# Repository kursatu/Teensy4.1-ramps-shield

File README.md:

# Teensy4.1-ramps-shield

This is a RAMPS shield/adapter for teensy4.1.\
The Marlin firmware now has support for teensy4.1.\
But, I couldn't find a ready-to-use HW.\
So, I've designed one for myself.\
It only has female headers at this time and I'll try to keep it this way.\
It is work in progress and not really in my priority list. But it is something super easy to do. \
The teensy4.1 work is still progressing, there may be pin changes and such.\
So I may not move very fast on it.\
Here is the schema https://github.com/kursatu/Teensy4.1-ramps-shield/blob/main/schema.png \
Here is the board https://github.com/kursatu/Teensy4.1-ramps-shield/blob/main/board.png \

Here is the pin mapping

Teensy4.1 | Mega2560/RAMPS
-|-
TODO | TODO

To do:
- [ ] Verify if all pins are properly mapped, using a RAMPS board and breadboard teensy4.1
- [ ] Get it verified by the people in github teensy4.1 thread
- [ ] Get it produced
- [ ] Find and way for people to order them inexpensively. Osh park charges $42 for 3 of them.

Completed tasks:
- [X] Complete all the pin connections. Completed on Oct/13/2020
- [X] Order RAMPS board. Completed on Oct/14/2020
Ordered this RAMP 1.6 board.\
They are supposedly pin compatible with RAMP 1.4 of reprap.\
https://www.amazon.com/gp/product/B07RF576WC/ref=ppx_yo_dt_b_asin_title_o00_s00?ie=UTF8&psc=1

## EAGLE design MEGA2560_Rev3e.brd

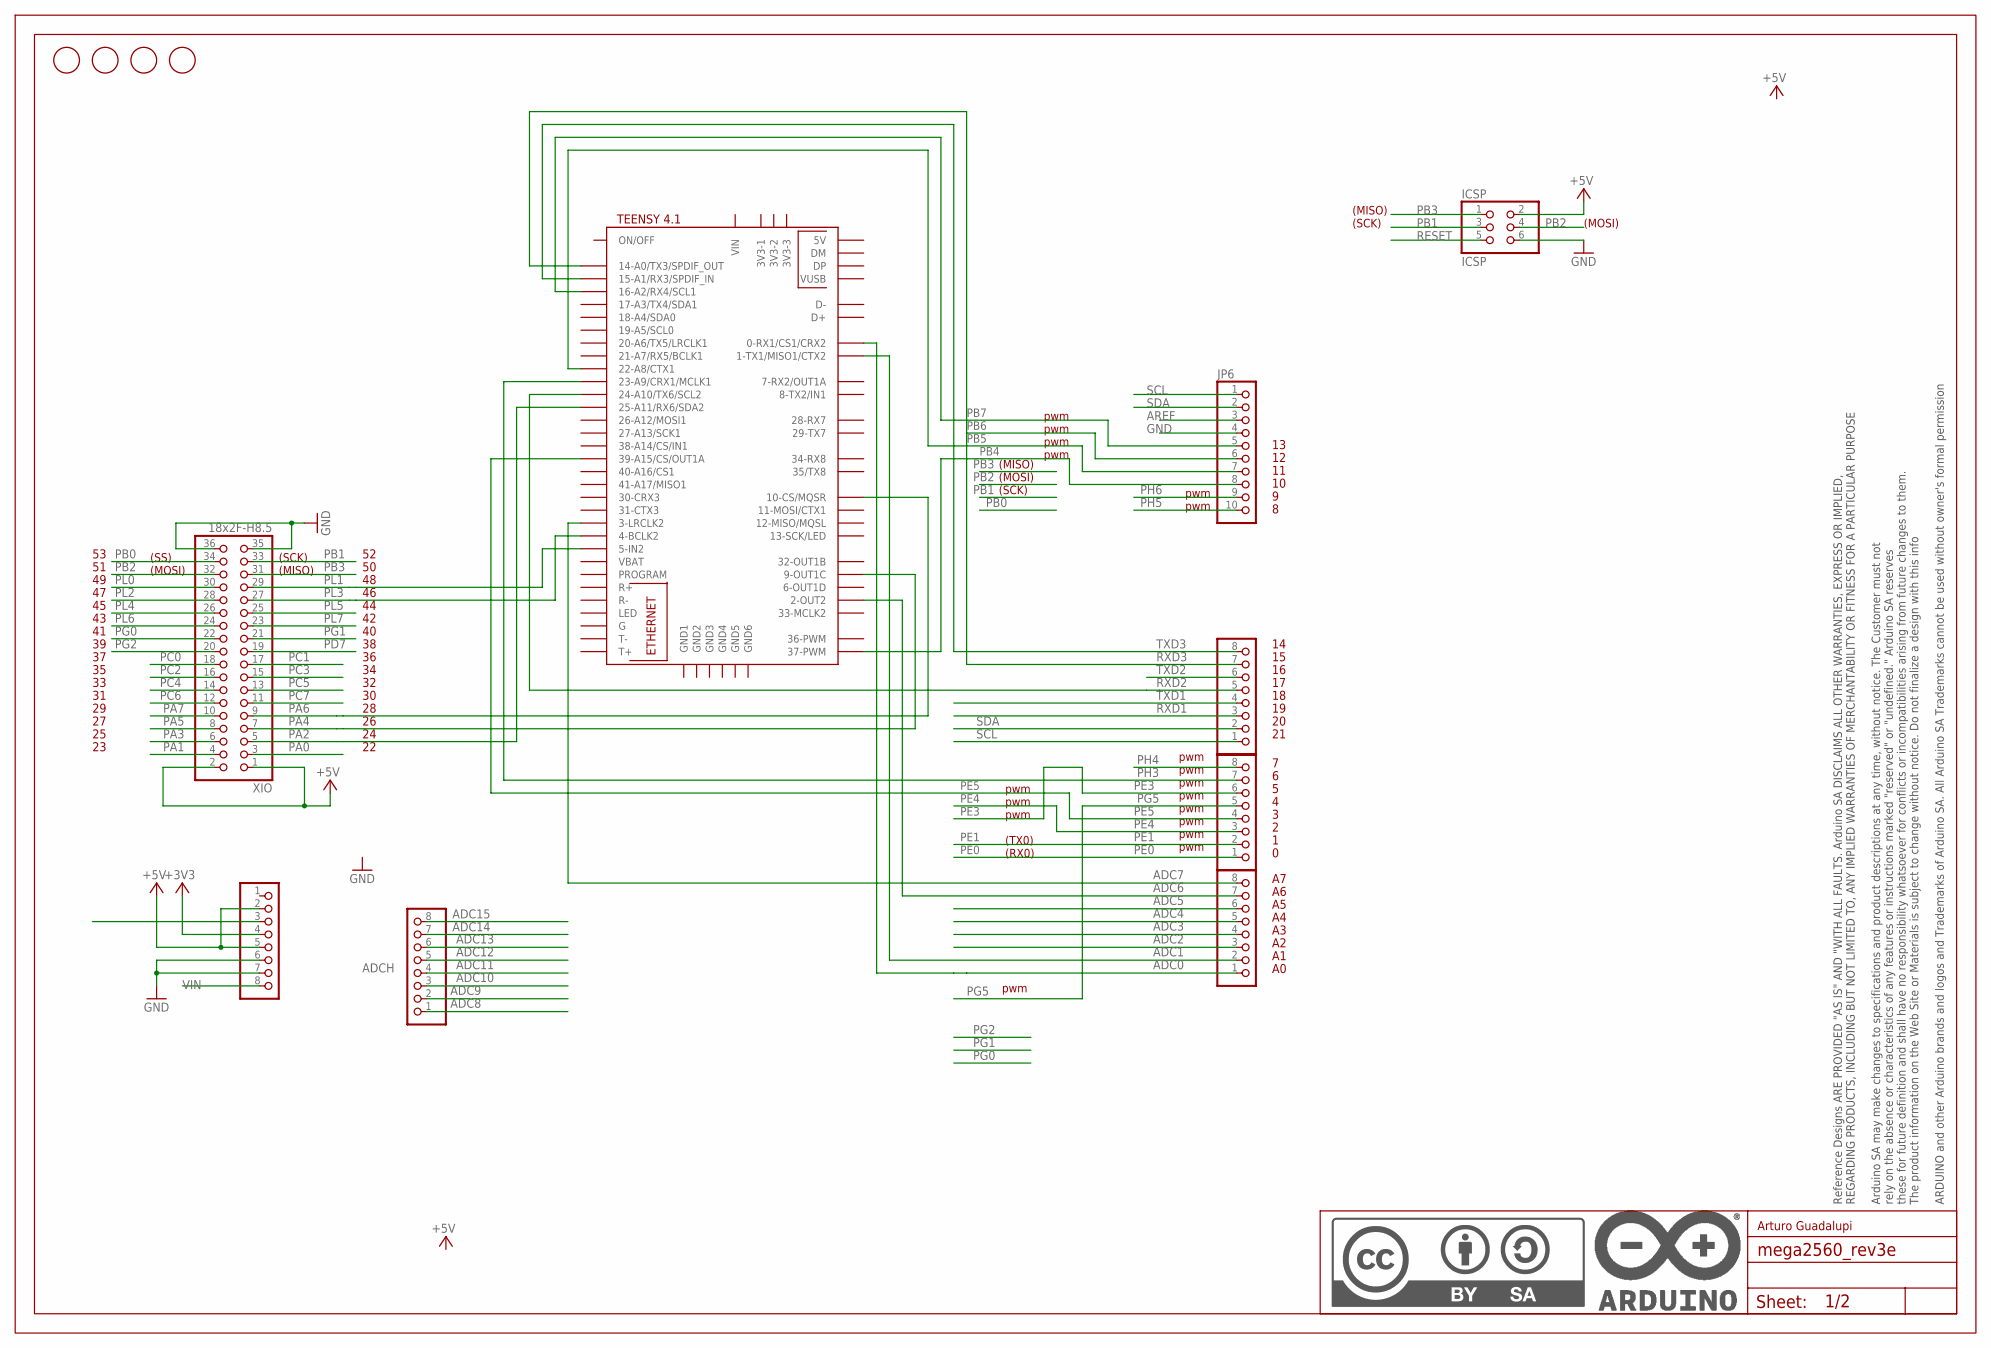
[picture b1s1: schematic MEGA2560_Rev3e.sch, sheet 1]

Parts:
ADCH: FH254-108DF08500V; 1X08
ADCL: FH254-108DF08500V; 1X08
COMMUNICATION: FH254-108DF08500V; 1X08
FD1, FD2, FD3, FD4: FIDUCIALMOUNT; FIDUCIA-MOUNT
ICSP: ICSP; 2X03
JP6: FH254-110DF08500V; 1X10
POWER: FH254-108DF08500V; 1X08
PWML: FH254-108DF08500V; 1X08
U$1: DNP; FRAME
U$3: TEENSY41
XIO: 18x2F-H8.5; 2X18

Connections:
+3V3: POWER.4
+5V: ICSP.2, POWER.2, POWER.5, XIO.1, XIO.2; also elsewhere on the board
ADC0: ADCL.1, U$3.0-RX1/CS1/CRX2
ADC1: ADCL.2, U$3.1-TX1/MISO1/CTX2
ADC2: ADCL.3
ADC3: ADCL.4
ADC4: ADCL.5
ADC5: ADCL.6
ADC6: ADCL.7, U$3.2-OUT2
ADC7: ADCL.8, U$3.3-LRCLK2
ADC8: ADCH.1
ADC9: ADCH.2
ADC10: ADCH.3
ADC11: ADCH.4
ADC12: ADCH.5
ADC13: ADCH.6
ADC14: ADCH.7
ADC15: ADCH.8
AREF: JP6.3
GND: ICSP.6, JP6.4, POWER.6, POWER.7, XIO.35, XIO.36; also elsewhere on the board
PA0: XIO.3
PA1: XIO.4
PA2: U$3.25-A11/RX6/SDA2, XIO.5
PA3: XIO.6
PA4: U$3.9-OUT1C, XIO.7
PA5: XIO.8
PA6: U$3.10-CS\MQSR (10-CS/MQSR), XIO.9
PA7: XIO.10
PB0: XIO.34
PB1: ICSP.3, XIO.33
PB2: ICSP.4, XIO.32
PB3: ICSP.1, XIO.31
PB4: JP6.8, U$3.37-PWM
PB5: JP6.7, U$3.22-A8/CTX1
PB6: JP6.6
PB7: JP6.5, U$3.16-A2/RX4/SCL1
PC0: XIO.18
PC1: XIO.17
PC2: XIO.16
PC3: XIO.15
PC4: XIO.14
PC5: XIO.13
PC6: XIO.12
PC7: XIO.11
PD7: XIO.19
PE0: PWML.1
PE1: PWML.2
PE3: PWML.6
PE4: PWML.3
PE5: PWML.4, U$3.39-A15/CS/OUT1A
PG0: XIO.22
PG1: XIO.21
PG2: XIO.20
PG5: PWML.5
PH3: PWML.7, U$3.23-A9/CRX1/MCLK1
PH4: PWML.8
PH5: JP6.10
PH6: JP6.9
PL0: XIO.30
PL1: U$3.5-IN2, XIO.29
PL2: XIO.28
PL3: U$3.4-BCLK2, XIO.27
PL4: XIO.26
PL5: XIO.25
PL6: XIO.24
PL7: XIO.23
RESET: ICSP.5, POWER.3
RXD1: COMMUNICATION.3
RXD2: COMMUNICATION.5, U$3.24-A10/TX6/SCL2
RXD3: COMMUNICATION.7, U$3.14-A0/TX3/SPDIF_OUT
SCL: COMMUNICATION.1, JP6.1
SDA: COMMUNICATION.2, JP6.2
TXD1: COMMUNICATION.4
TXD2: COMMUNICATION.6
TXD3: COMMUNICATION.8, U$3.15-A1/RX3/SPDIF_IN
VIN: POWER.8

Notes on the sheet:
(SCK)
(MISO)
(MOSI)
pwm
(TX0)
(RX0)
(SS)
Arturo Guadalupi

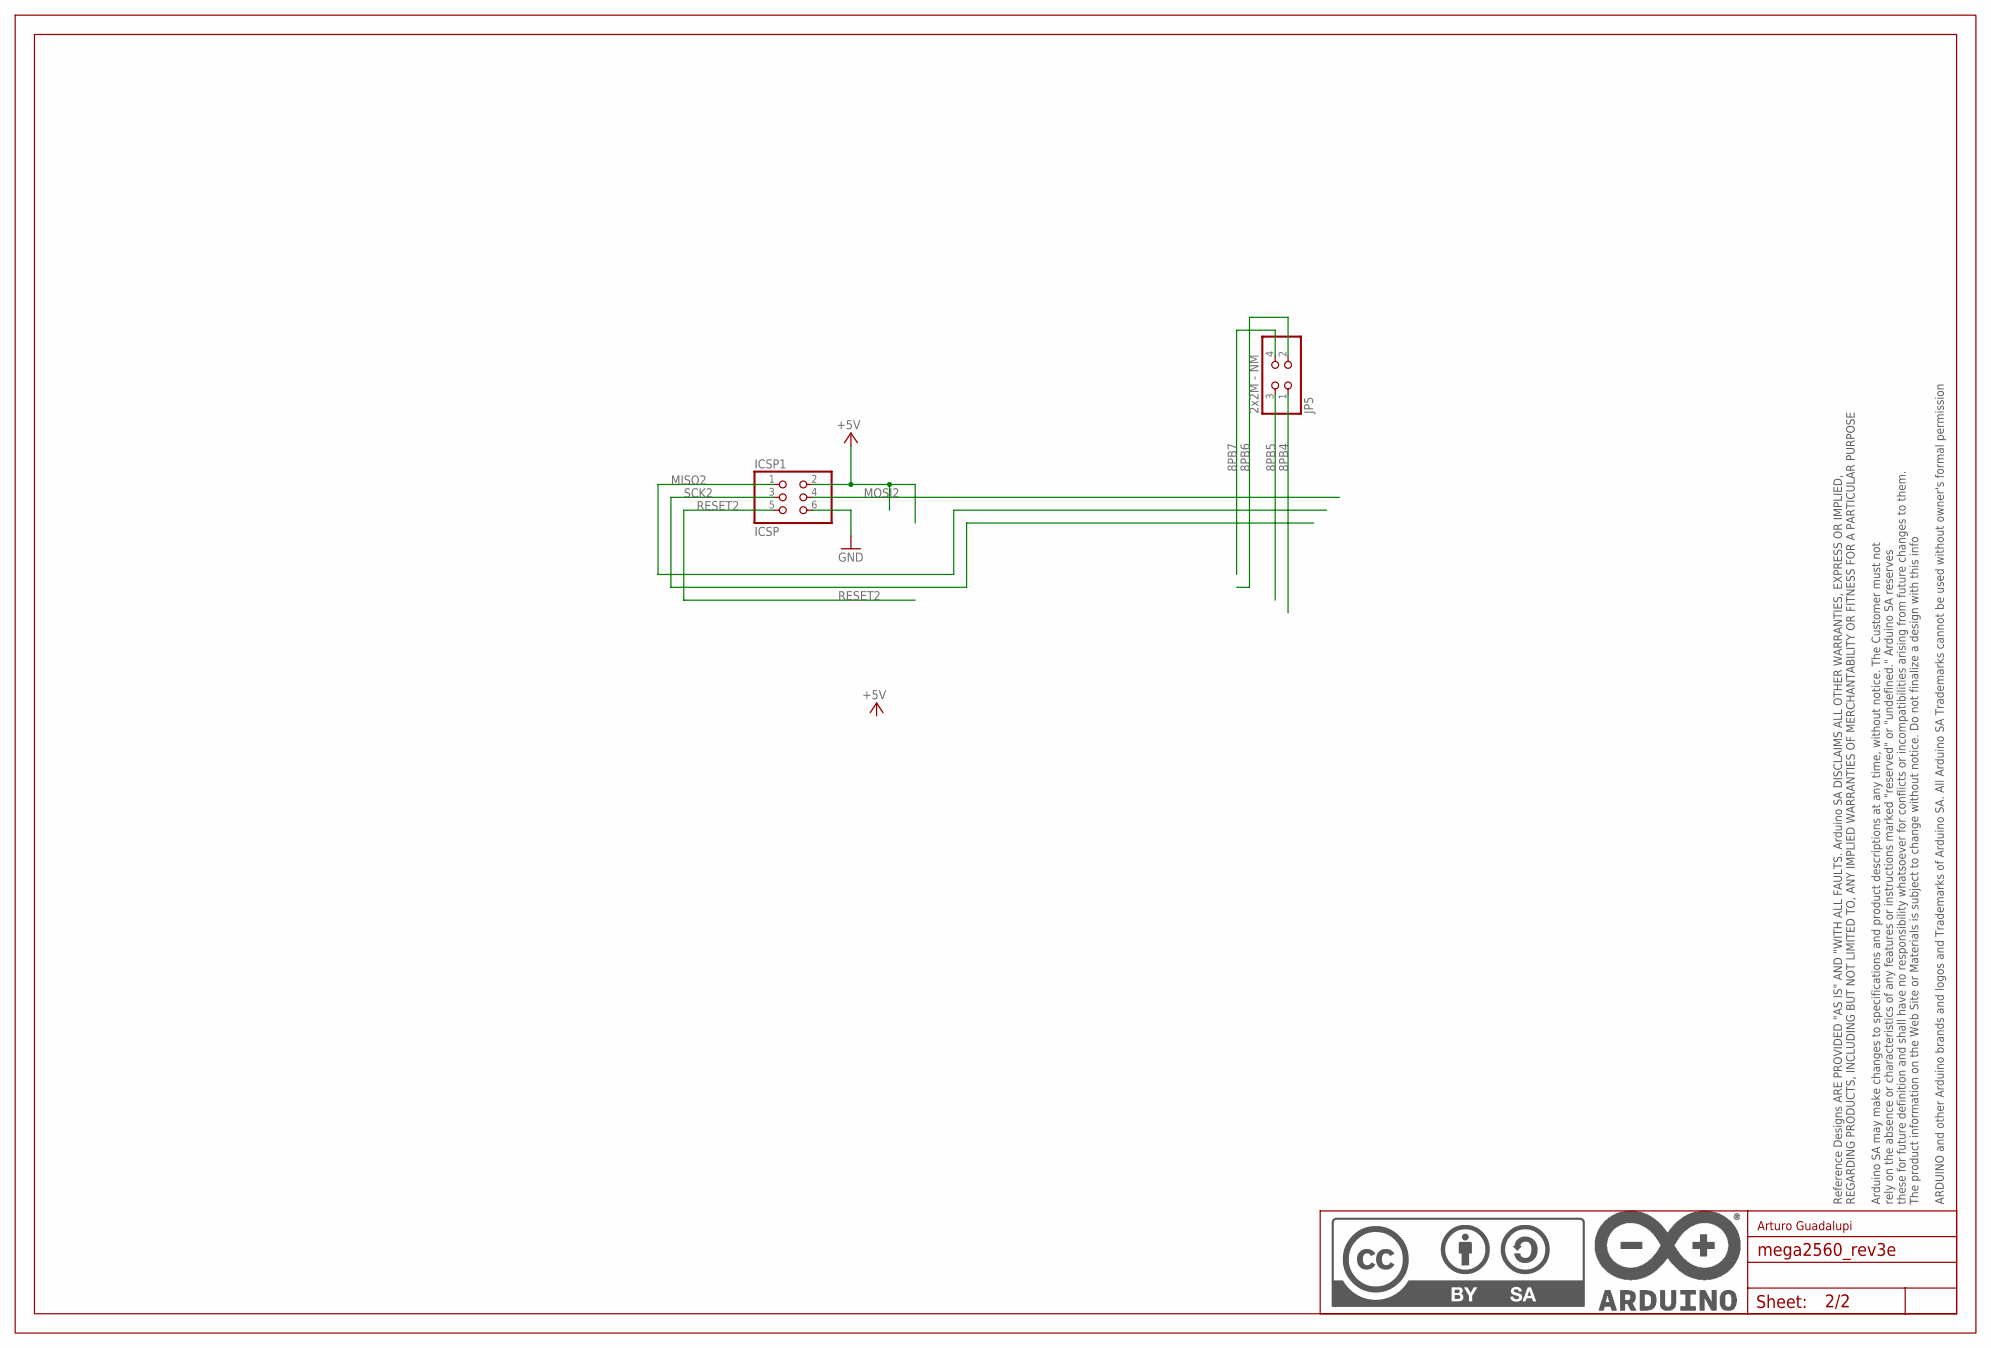
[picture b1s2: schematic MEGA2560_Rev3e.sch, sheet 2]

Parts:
ICSP1: ICSP; 2X03
JP5: 2x2M - NM; 2X02
U$2: DNP; FRAME

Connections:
8PB4: JP5.1
8PB5: JP5.3
8PB6: JP5.2
8PB7: JP5.4
+5V: ICSP1.2; also elsewhere on the board
GND: ICSP1.6; also elsewhere on the board
MISO2: ICSP1.1
MOSI2: ICSP1.4
RESET2: ICSP1.5
SCK2: ICSP1.3

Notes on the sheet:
Arturo Guadalupi

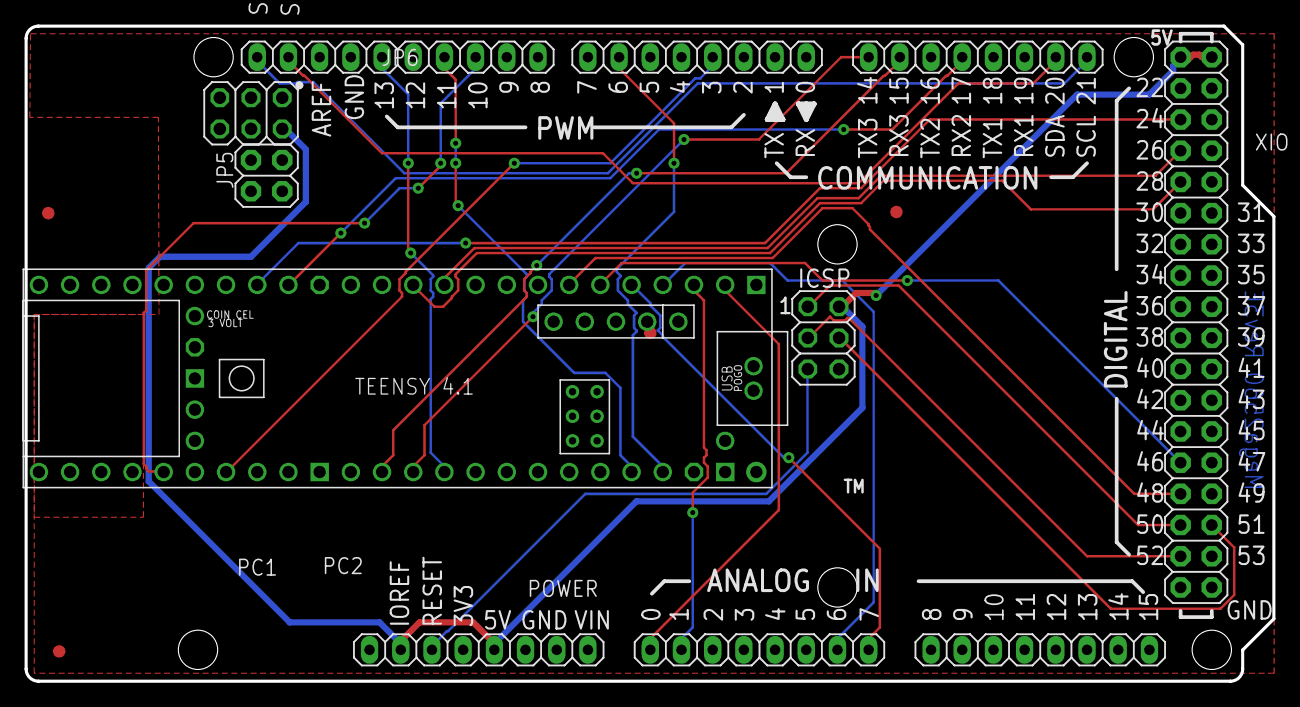
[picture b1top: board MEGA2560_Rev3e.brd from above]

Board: 2 copper layers, 101.6 x 53.3 mm, 17 parts (0 on the bottom side), 25 nets.

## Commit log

2020-10-14 Create README.md
    This is a RAMPS shield for teensy4.1.
    The Marlin firmware now has support for teensy4.1.
    There are no ready-to-use HW at this time.
    So, I've designed one for myself.
    It is work in progress and not really in my priority list.
    The teensy4.1 work is still progressing, there may be pin changes and such.
2020-10-14 Update schema image
2020-10-14 Add board image

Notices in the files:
parts and their libraries:
Arduino-utility: Copyright (c) 2016-2017 Arduino LLC.  All right reserved.
